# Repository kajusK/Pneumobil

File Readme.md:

Pneumobil control and telemetry system
======================================

This repository contains source code and board design for control system
of pneumobil racing car Falcon from Brno University of Technology.

Parts
-----
 * HMI - Human Machine Interface - LCD touch screen and telemetry board

 * ECU - Engine Control Unit - Control system of pneumatic propulsion system

 * SDU - Speed Display Unit

 * PSU - Power Supply Unit

 * Radio2usb - Telemetry receiving system

Description
-----------
Placement in the car

Python telemetry program

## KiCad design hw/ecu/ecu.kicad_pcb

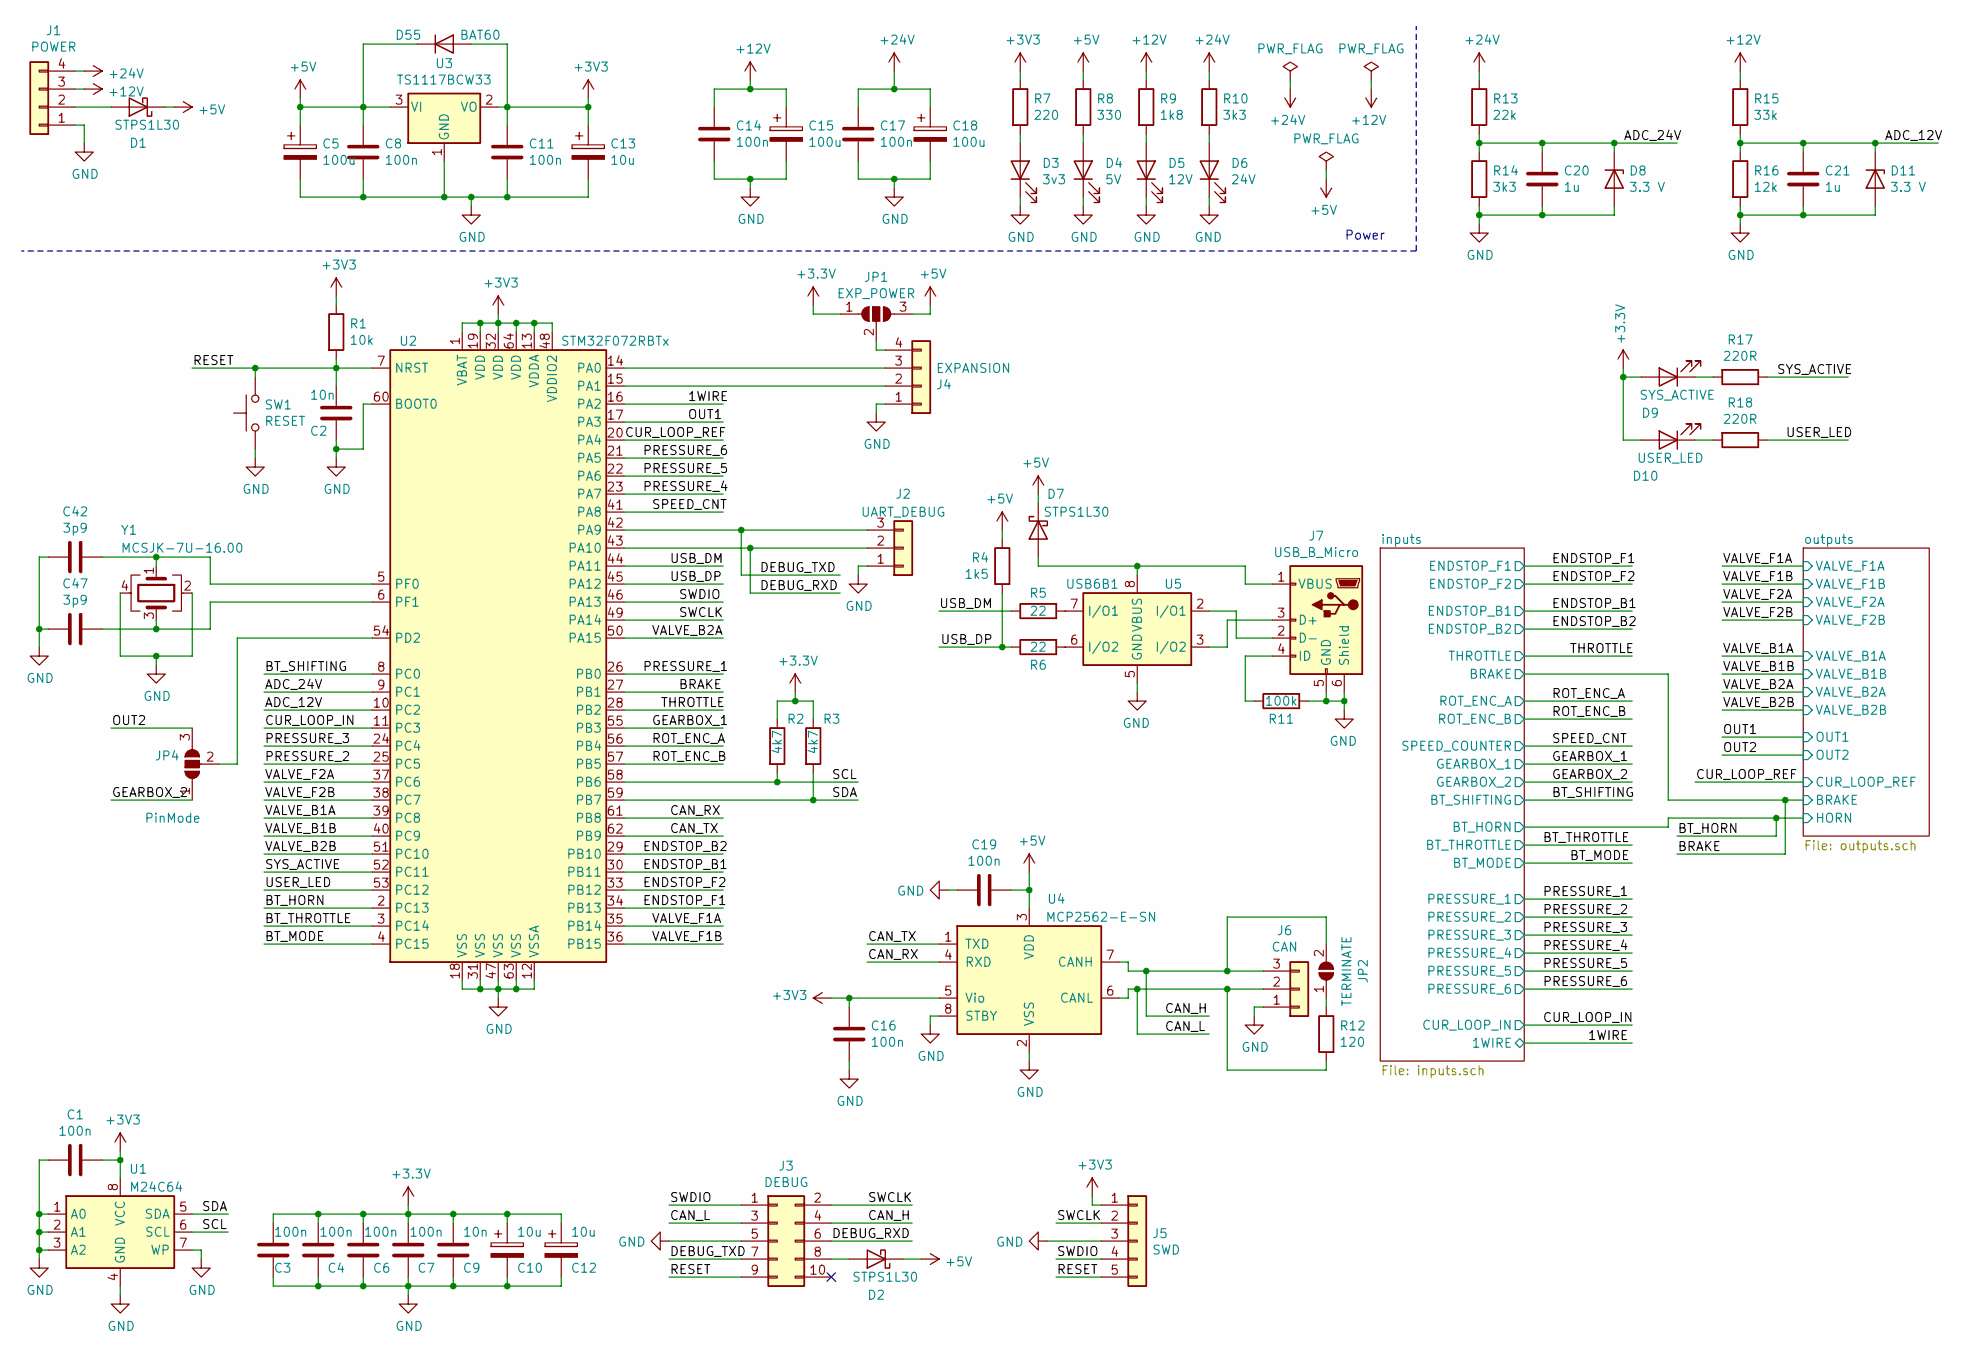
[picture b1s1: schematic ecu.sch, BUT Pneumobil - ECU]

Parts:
C1, C3, C4, C6, C7, C8, C11, C14, C16, C17, C19: 100n; C_0805_2012Metric
C2, C9: 10n; C_0805_2012Metric
C5, C15, C18: 100u; CP_Elec_6.3x7.7
C10, C12, C13: 10u; C_0805_2012Metric
C20, C21: 1u; C_0805_2012Metric
C42, C47: 3p9; C_0805_2012Metric
D1, D2, D7: STPS1L30; D_SMB
D3: 3v3; LED_1206_3216Metric
D4: 5V; LED_1206_3216Metric
D5: 12V; LED_1206_3216Metric
D6: 24V; LED_1206_3216Metric
D8, D11: 3.3 V; D_SOD-523
D9: SYS_ACTIVE; LED_1206_3216Metric
D10: USER_LED; LED_1206_3216Metric
D55: BAT60; D_SOD-323
J1: POWER; PhoenixContact_MCV_1,5_4-G-3.5_1x04_P3.50mm_Vertical
J2: UART_DEBUG; PinHeader_1x03_P2.54mm_Vertical
J3: DEBUG; IDC-Header_2x05_P2.54mm_Vertical
J4: EXPANSION; Molex_KK-254_AE-6410-04A_1x04_P2.54mm_Vertical
J5: SWD; PinHeader_1x05_P2.54mm_Vertical
J6: CAN; Molex_Nano-Fit_105309-xx03_1x03_P2.50mm_Vertical
J7: USB_B_Micro; USB_Micro-B_Molex-105133-0001
JP1: EXP_POWER; SolderJumper-3_P1.3mm_Open_Pad1.0x1.5mm_NumberLabels
JP2: TERMINATE; SolderJumper-2_P1.3mm_Open_Pad1.0x1.5mm
JP4: PinMode; SolderJumper-3_P1.3mm_Open_Pad1.0x1.5mm
R1: 10k; R_0805_2012Metric
R2, R3: 4k7; R_0805_2012Metric
R4: 1k5; R_0805_2012Metric
R5, R6: 22; R_0805_2012Metric
R7: 220; R_0805_2012Metric
R8: 330; R_0805_2012Metric
R9: 1k8; R_0805_2012Metric
R10, R14: 3k3; R_0805_2012Metric
R11: 100k; R_0805_2012Metric
R12: 120; R_0805_2012Metric
R13: 22k; R_0805_2012Metric
R15: 33k; R_0805_2012Metric
R16: 12k; R_0805_2012Metric
R17, R18: 220R; R_0805_2012Metric
SW1: RESET; SW_SPST_PTS645
U1: M24C64; SOIC-8_3.9x4.9mm_P1.27mm
U2: STM32F072RBTx; LQFP-64_10x10mm_P0.5mm
U3: TS1117BCW33; SOT-223-3_TabPin2
U4: MCP2562-E-SN; SOIC-8_3.9x4.9mm_P1.27mm
U5: USB6B1; SOIC-8_3.9x4.9mm_P1.27mm
Y1: MCSJK-7U-16.00; Crystal_SMD_3225-4Pin_3.2x2.5mm

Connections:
+5V: C5.1, C8.1, C19.1, D1.1 (K), D2.1 (K), D7.1 (K), D55.1 (K), JP1.3 (B), R4.1, R8.1, U3.3 (VI), U4.3 (VDD)
+12V: C14.1, C15.1, J1.3, R9.1, R15.1; also elsewhere on the board
+24V: C17.1, C18.1, J1.4, R10.1, R13.1; also elsewhere on the board
/1WIRE: U2.16 (PA2); also elsewhere on the board
/ADC_12V: C21.1, D11.1 (K), R15.2, R16.1, U2.10 (PC2)
/ADC_24V: C20.1, D8.1 (K), R13.2, R14.1, U2.9 (PC1)
/BRAKE: U2.27 (PB1); also elsewhere on the board
/BT_HORN: U2.2 (PC13); also elsewhere on the board
/BT_MODE: U2.4 (PC15); also elsewhere on the board
/BT_SHIFTING: U2.8 (PC0); also elsewhere on the board
/BT_THROTTLE: U2.3 (PC14); also elsewhere on the board
/CAN_H: J3.4, J6.3, JP2.2 (B), U4.7 (CANH)
/CAN_L: J3.3, J6.2, R12.2, U4.6 (CANL)
/CAN_RX: U2.61 (PB8), U4.4 (RXD)
/CAN_TX: U2.62 (PB9), U4.1 (TXD)
/CUR_LOOP_IN: U2.11 (PC3); also elsewhere on the board
/CUR_LOOP_REF: U2.20 (PA4); also elsewhere on the board
/DEBUG_RXD: J2.2, J3.6, U2.43 (PA10)
/DEBUG_TXD: J2.3, J3.7, U2.42 (PA9)
/ENDSTOP_B1: U2.30 (PB11); also elsewhere on the board
/ENDSTOP_B2: U2.29 (PB10); also elsewhere on the board
/ENDSTOP_F1: U2.34 (PB13); also elsewhere on the board
/ENDSTOP_F2: U2.33 (PB12); also elsewhere on the board
/GEARBOX_1: U2.55 (PB3); also elsewhere on the board
/GEARBOX_2: JP4.1 (A); also elsewhere on the board
/OUT1: U2.17 (PA3); also elsewhere on the board
/OUT2: JP4.3 (B); also elsewhere on the board
/PRESSURE_1: U2.26 (PB0); also elsewhere on the board
/PRESSURE_2: U2.25 (PC5); also elsewhere on the board
/PRESSURE_3: U2.24 (PC4); also elsewhere on the board
/PRESSURE_4: U2.23 (PA7); also elsewhere on the board
/PRESSURE_5: U2.22 (PA6); also elsewhere on the board
/PRESSURE_6: U2.21 (PA5); also elsewhere on the board
/RESET: C2.1, J3.9, J5.5, R1.2, SW1.2, U2.7 (NRST)
/ROT_ENC_A: U2.56 (PB4); also elsewhere on the board
/ROT_ENC_B: U2.57 (PB5); also elsewhere on the board
/SCL: R2.2, U1.6 (SCL), U2.58 (PB6)
/SDA: R3.2, U1.5 (SDA), U2.59 (PB7)
/SPEED_CNT: U2.41 (PA8); also elsewhere on the board
/SWCLK: J3.2, J5.2, U2.49 (PA14)
/SWDIO: J3.1, J5.4, U2.46 (PA13)
/SYS_ACTIVE: R17.1, U2.52 (PC11)
/THROTTLE: U2.28 (PB2); also elsewhere on the board
/USB_DM: R5.1, U2.44 (PA11)
/USB_DP: R4.2, R6.1, U2.45 (PA12)
/USER_LED: R18.1, U2.53 (PC12)
/VALVE_B1A: U2.39 (PC8); also elsewhere on the board
/VALVE_B1B: U2.40 (PC9); also elsewhere on the board
/VALVE_B2A: U2.50 (PA15); also elsewhere on the board
/VALVE_B2B: U2.51 (PC10); also elsewhere on the board
/VALVE_F1A: U2.35 (PB14); also elsewhere on the board
/VALVE_F1B: U2.36 (PB15); also elsewhere on the board
/VALVE_F2A: U2.37 (PC6); also elsewhere on the board
/VALVE_F2B: U2.38 (PC7); also elsewhere on the board
GND: C1.2, C2.2, C3.2, C4.2, C5.2, C6.2, C7.2, C8.2, C9.2, C10.2, C11.2, C12.2, C13.2, C14.2, C15.2, C16.2, C17.2, C18.2, C19.2, C20.2, C21.2, C42.2, C47.2, D3.1 (K), D4.1 (K), D5.1 (K), D6.1 (K), D8.2 (A), D11.2 (A), J1.1, J2.1, J3.5, J4.1, J5.3, J6.1, J7.5 (GND), J7.6 (Shield), R11.2, R14.2, R16.2, SW1.1, U1.1 (A0), U1.2 (A1), U1.3 (A2), U1.4 (GND), U1.7 (WP), U2.12 (VSSA), U2.18 (VSS), U2.31 (VSS), U2.47 (VSS), U2.60 (BOOT0), U2.63 (VSS), U3.1 (GND), U4.2 (VSS), U4.8 (STBY), U5.4 (GND), U5.5 (GND), Y1.2, Y1.4; also elsewhere on the board
unnamed: C42.1, U2.5 (PF0), Y1.1
unnamed: C47.1, U2.6 (PF1), Y1.3
unnamed: D1.2 (A), J1.2
unnamed: D2.2 (A), J3.8
unnamed: D3.2 (A), R7.2
unnamed: D4.2 (A), R8.2
unnamed: D5.2 (A), R9.2
unnamed: D6.2 (A), R10.2
unnamed: D7.2 (A), J7.1 (VBUS), U5.1 (VBUS), U5.8 (VBUS)
unnamed: D9.1 (K), R17.2
unnamed: D10.1 (K), R18.2
unnamed: J4.2, U2.15 (PA1)
unnamed: J4.3, U2.14 (PA0)
unnamed: J4.4, JP1.2 (C)
unnamed: J7.2 (D-), U5.2 (I/O1)
unnamed: J7.3 (D+), U5.3 (I/O2)
unnamed: J7.4 (ID), R11.1
unnamed: JP2.1 (A), R12.1
unnamed: JP4.2 (C), U2.54 (PD2)
unnamed: R5.2, U5.7 (I/O1)
unnamed: R6.2, U5.6 (I/O2)

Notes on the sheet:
Power

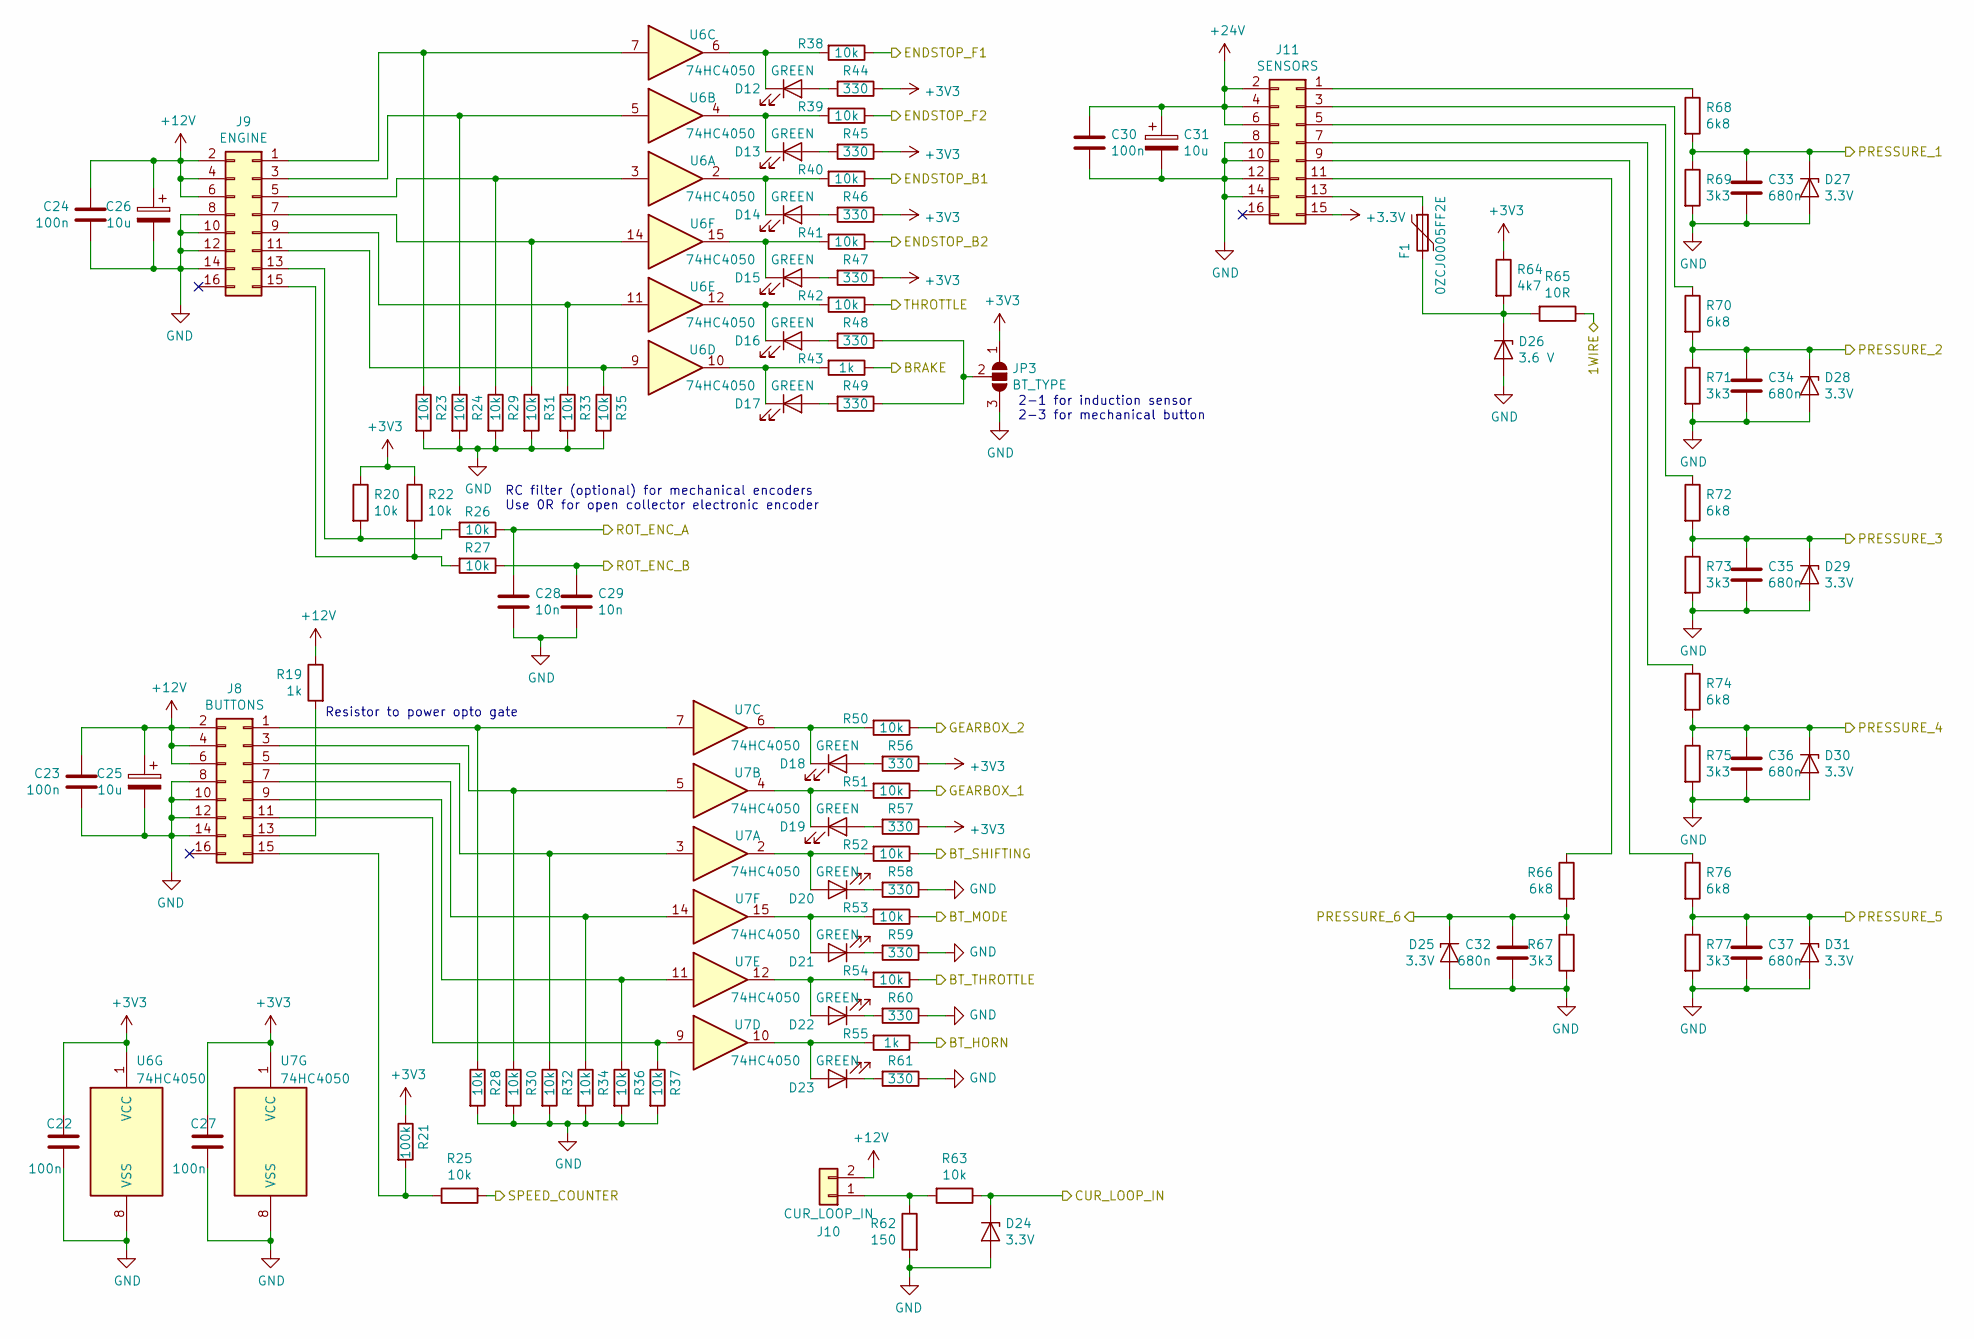
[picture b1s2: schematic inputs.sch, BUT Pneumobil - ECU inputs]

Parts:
C22, C23, C24, C27, C30: 100n; C_0805_2012Metric
C25, C26, C31: 10u; C_0805_2012Metric
C28, C29: 10n; C_0805_2012Metric
C32, C33, C34, C35, C36, C37: 680n; C_0805_2012Metric
D12, D13, D14, D15, D16, D17, D18, D19, D20, D21, D22, D23: GREEN; LED_1206_3216Metric
D24, D25, D27, D28, D29, D30, D31: 3.3V; D_SOD-523
D26: 3.6 V; D_MELF
F1: 0ZCJ0005FF2E; Fuse_1206_3216Metric
J8: BUTTONS; IDC-Header_2x08_P2.54mm_Vertical_Lock
J9: ENGINE; IDC-Header_2x08_P2.54mm_Vertical_Lock
J10: CUR_LOOP_IN; PhoenixContact_MCV_1,5_2-G-3.5_1x02_P3.50mm_Vertical
J11: SENSORS; IDC-Header_2x08_P2.54mm_Vertical_Lock
JP3: BT_TYPE; SolderJumper-3_P1.3mm_Open_Pad1.0x1.5mm
R19, R43, R55: 1k; R_0805_2012Metric
R20, R22, R23, R24, R25, R26, R27, R28, R29, R30, R31, R32, R33, R34, R35, R36, R37, R38, R39, R40, R41, R42, R50, R51, R52, R53, R54, R63: 10k; R_0805_2012Metric
R21: 100k; R_0805_2012Metric
R44, R45, R46, R47, R48, R49, R56, R57, R58, R59, R60, R61: 330; R_0805_2012Metric
R62: 150; R_0805_2012Metric
R64: 4k7; R_0805_2012Metric
R65: 10R; R_0805_2012Metric
R66, R68, R70, R72, R74, R76: 6k8; R_0805_2012Metric
R67, R69, R71, R73, R75, R77: 3k3; R_0805_2012Metric
U6, U7: 74HC4050; SOIC-16_3.9x9.9mm_P1.27mm

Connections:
+12V: C23.1, C24.1, C25.1, C26.1, J8.2, J8.4, J8.6, J9.2, J9.4, J9.6, J10.2, R19.1; also elsewhere on the board
+24V: C30.1, C31.1, J11.2, J11.4, J11.6; also elsewhere on the board
/1WIRE: R65.1; also elsewhere on the board
/BRAKE: R43.1; also elsewhere on the board
/BT_HORN: R55.1; also elsewhere on the board
/BT_MODE: R53.1; also elsewhere on the board
/BT_SHIFTING: R52.1; also elsewhere on the board
/BT_THROTTLE: R54.1; also elsewhere on the board
/CUR_LOOP_IN: D24.1 (K), R63.1; also elsewhere on the board
/ENDSTOP_B1: R40.1; also elsewhere on the board
/ENDSTOP_B2: R41.1; also elsewhere on the board
/ENDSTOP_F1: R38.1; also elsewhere on the board
/ENDSTOP_F2: R39.1; also elsewhere on the board
/GEARBOX_1: R51.1; also elsewhere on the board
/GEARBOX_2: R50.1; also elsewhere on the board
/PRESSURE_1: C33.1, D27.1 (K), R68.2, R69.1; also elsewhere on the board
/PRESSURE_2: C34.1, D28.1 (K), R70.2, R71.1; also elsewhere on the board
/PRESSURE_3: C35.1, D29.1 (K), R72.2, R73.1; also elsewhere on the board
/PRESSURE_4: C36.1, D30.1 (K), R74.2, R75.1; also elsewhere on the board
/PRESSURE_5: C37.1, D31.1 (K), R76.2, R77.1; also elsewhere on the board
/PRESSURE_6: C32.1, D25.1 (K), R66.2, R67.1; also elsewhere on the board
/ROT_ENC_A: C28.1, R26.1; also elsewhere on the board
/ROT_ENC_B: C29.1, R27.1; also elsewhere on the board
/SPEED_CNT: R25.2; also elsewhere on the board
/THROTTLE: R42.1; also elsewhere on the board
GND: C22.2, C23.2, C24.2, C25.2, C26.2, C27.2, C28.2, C29.2, C30.2, C31.2, C32.2, C33.2, C34.2, C35.2, C36.2, C37.2, D24.2 (A), D25.2 (A), D26.2 (A), D27.2 (A), D28.2 (A), D29.2 (A), D30.2 (A), D31.2 (A), J8.8, J8.10, J8.12, J8.14, J9.8, J9.10, J9.12, J9.14, J11.8, J11.10, J11.12, J11.14, JP3.3 (B), R23.2, R24.2, R28.2, R29.2, R30.2, R31.2, R32.2, R33.2, R34.2, R35.2, R36.2, R37.2, R58.1, R59.1, R60.1, R61.1, R62.2, R67.2, R69.2, R71.2, R73.2, R75.2, R77.2, U6.8 (VSS), U7.8 (VSS); also elsewhere on the board
unnamed: D12.1 (K), R38.2, U6.6
unnamed: D12.2 (A), R44.2
unnamed: D13.1 (K), R39.2, U6.4
unnamed: D13.2 (A), R45.2
unnamed: D14.1 (K), R40.2, U6.2
unnamed: D14.2 (A), R46.2
unnamed: D15.1 (K), R41.2, U6.15
unnamed: D15.2 (A), R47.2
unnamed: D16.1 (K), R42.2, U6.12
unnamed: D16.2 (A), R48.2
unnamed: D17.1 (K), R43.2, U6.10
unnamed: D17.2 (A), R49.2
unnamed: D18.1 (K), R50.2, U7.6
unnamed: D18.2 (A), R56.2
unnamed: D19.1 (K), R51.2, U7.4
unnamed: D19.2 (A), R57.2
unnamed: D20.1 (K), R58.2
unnamed: D20.2 (A), R52.2, U7.2
unnamed: D21.1 (K), R59.2
unnamed: D21.2 (A), R53.2, U7.15
unnamed: D22.1 (K), R60.2
unnamed: D22.2 (A), R54.2, U7.12
unnamed: D23.1 (K), R61.2
unnamed: D23.2 (A), R55.2, U7.10
unnamed: D26.1 (K), F1.2, R64.2, R65.2
unnamed: F1.1, J11.13
unnamed: J8.1, R28.1, U7.7
unnamed: J8.3, R30.1, U7.5
unnamed: J8.5, R32.1, U7.3
unnamed: J8.7, R34.1, U7.14
unnamed: J8.9, R36.1, U7.11
unnamed: J8.11, R37.1, U7.9
unnamed: J8.13, R19.2
unnamed: J8.15, R21.2, R25.1
unnamed: J9.1, R23.1, U6.7
unnamed: J9.3, R24.1, U6.5
unnamed: J9.5, R29.1, U6.3
unnamed: J9.7, R31.1, U6.14
unnamed: J9.9, R33.1, U6.11
unnamed: J9.11, R35.1, U6.9
unnamed: J9.13, R20.2, R26.2
unnamed: J9.15, R22.2, R27.2
unnamed: J10.1, R62.1, R63.2
unnamed: J11.1, R68.1
unnamed: J11.3, R70.1
unnamed: J11.5, R72.1
unnamed: J11.7, R74.1
unnamed: J11.9, R76.1
unnamed: J11.11, R66.1
unnamed: JP3.2 (C), R48.1, R49.1

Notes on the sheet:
Resistor to power opto gate
RC filter (optional) for mechanical encoders Use 0R for open collector electronic encoder
2-1 for induction sensor 2-3 for mechanical button

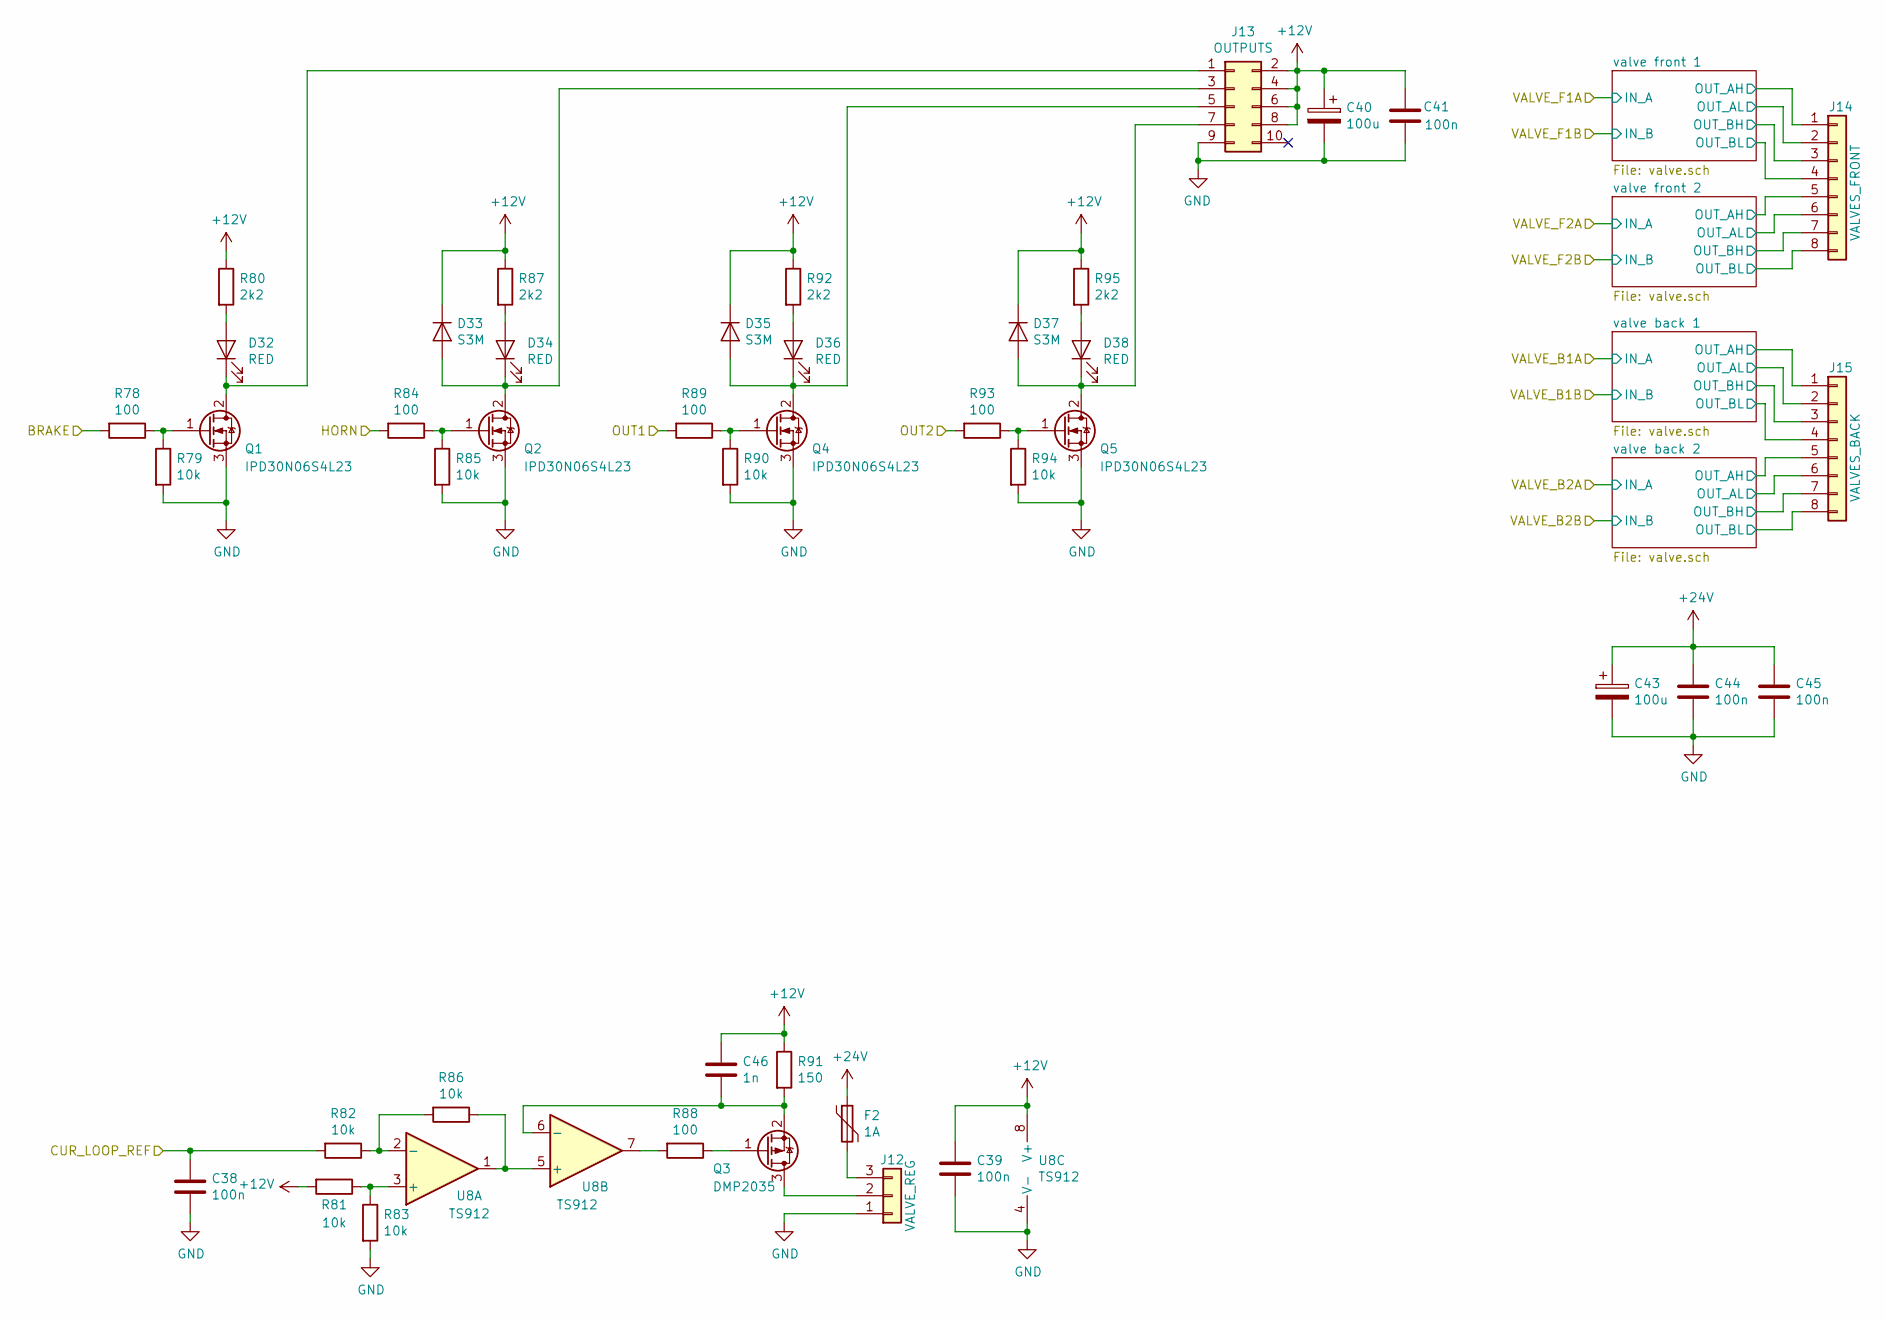
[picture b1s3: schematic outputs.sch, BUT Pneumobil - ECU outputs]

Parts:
C38, C39, C41, C44, C45: 100n; C_0805_2012Metric
C40, C43: 100u; CP_Elec_6.3x7.7
C46: 1n; C_0805_2012Metric
D32, D34, D36, D38: RED; LED_1206_3216Metric
D33, D35, D37: S3M; D_SMB
F2: 1A; Fuse_1206_3216Metric
J12: VALVE_REG; PhoenixContact_MCV_1,5_3-G-3.5_1x03_P3.50mm_Vertical
J13: OUTPUTS; IDC-Header_2x05_P2.54mm_Vertical_Lock
J14: VALVES_FRONT; PhoenixContact_MCV_1,5_8-G-3.5_1x08_P3.50mm_Vertical
J15: VALVES_BACK; PhoenixContact_MCV_1,5_8-G-3.5_1x08_P3.50mm_Vertical
Q1, Q2, Q4, Q5: IPD30N06S4L23; TO-252-2
Q3: DMP2035; SOT-23
R78, R84, R88, R89, R93: 100; R_0805_2012Metric
R79, R81, R82, R83, R85, R86, R90, R94: 10k; R_0805_2012Metric
R80, R87, R92, R95: 2k2; R_0805_2012Metric
R91: 150; R_0805_2012Metric
U8: TS912; SOIC-8_3.9x4.9mm_P1.27mm

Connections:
+12V: C39.1, C40.1, C41.1, C46.1, D33.1 (K), D35.1 (K), D37.1 (K), J13.2, J13.4, J13.6, J13.8, R80.1, R81.2, R87.1, R91.1, R92.1, R95.1, U8.8 (V+); also elsewhere on the board
+24V: C43.1, C44.1, C45.1, F2.1, J14.1, J14.3, J14.5, J14.7, J15.1, J15.3, J15.5, J15.7; also elsewhere on the board
/BRAKE: R78.2; also elsewhere on the board
/BT_HORN: R84.2; also elsewhere on the board
/CUR_LOOP_REF: C38.1, R82.2; also elsewhere on the board
/OUT1: R89.2; also elsewhere on the board
/OUT2: R93.2; also elsewhere on the board
/outputs/valve back 1/OUT_AL: J15.2; also elsewhere on the board
/outputs/valve back 1/OUT_BL: J15.4; also elsewhere on the board
/outputs/valve back 2/OUT_AL: J15.6; also elsewhere on the board
/outputs/valve back 2/OUT_BL: J15.8; also elsewhere on the board
/outputs/valve front 1/OUT_AL: J14.2; also elsewhere on the board
/outputs/valve front 1/OUT_BL: J14.4; also elsewhere on the board
/outputs/valve front 2/OUT_AL: J14.6; also elsewhere on the board
/outputs/valve front 2/OUT_BL: J14.8; also elsewhere on the board
GND: C38.2, C39.2, C40.2, C41.2, C43.2, C44.2, C45.2, J12.1, J13.9, Q1.3 (S), Q2.3 (S), Q4.3 (S), Q5.3 (S), R79.2, R83.2, R85.2, R90.2, R94.2, U8.4 (V-); also elsewhere on the board
unnamed: C46.2, Q3.2 (S), R91.2, U8.6 (-)
unnamed: D32.1 (K), J13.1, Q1.2 (D)
unnamed: D32.2 (A), R80.2
unnamed: D33.2 (A), D34.1 (K), J13.3, Q2.2 (D)
unnamed: D34.2 (A), R87.2
unnamed: D35.2 (A), D36.1 (K), J13.5, Q4.2 (D)
unnamed: D36.2 (A), R92.2
unnamed: D37.2 (A), D38.1 (K), J13.7, Q5.2 (D)
unnamed: D38.2 (A), R95.2
unnamed: F2.2, J12.3
unnamed: J12.2, Q3.3 (D)
unnamed: Q1.1 (G), R78.1, R79.1
unnamed: Q2.1 (G), R84.1, R85.1
unnamed: Q3.1 (G), R88.1
unnamed: Q4.1 (G), R89.1, R90.1
unnamed: Q5.1 (G), R93.1, R94.1
unnamed: R81.1, R83.1, U8.3 (+)
unnamed: R82.1, R86.2, U8.2 (-)
unnamed: R86.1, U8.1, U8.5 (+)
unnamed: R88.2, U8.7

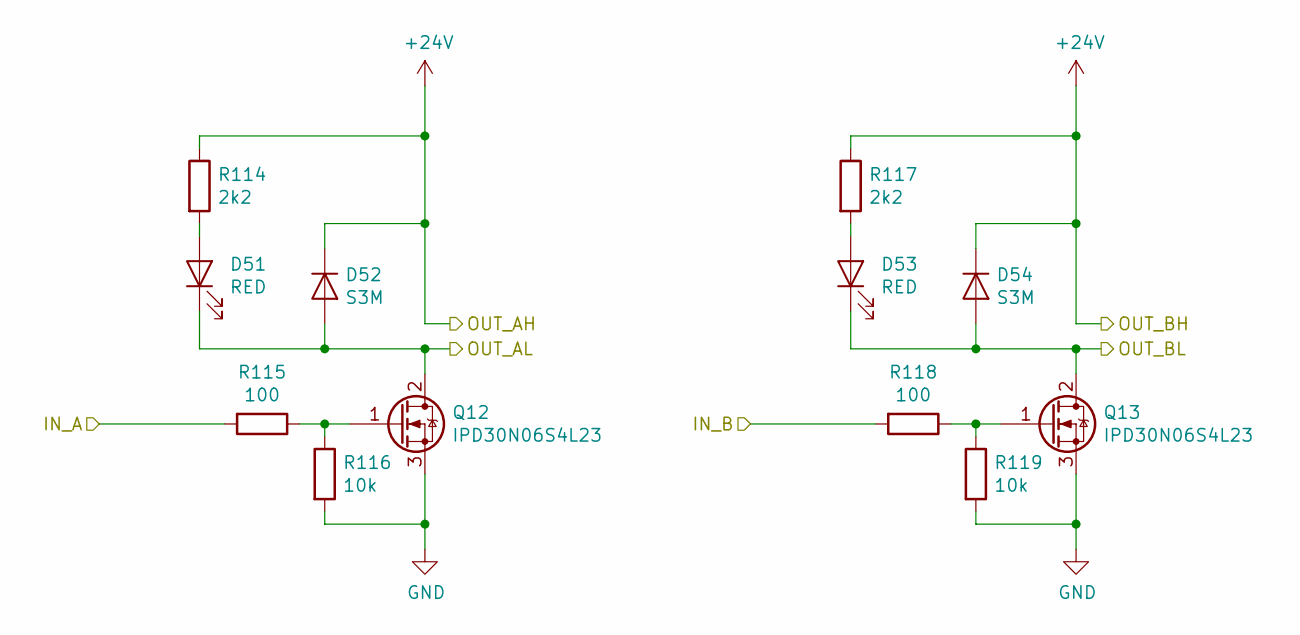
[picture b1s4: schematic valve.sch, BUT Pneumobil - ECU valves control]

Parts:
D39, D41: RED; LED_1206_3216Metric
D40, D42: S3M; D_SMB
Q6, Q7: IPD30N06S4L23; TO-252-2
R96, R99: 2k2; R_0805_2012Metric
R97, R100: 100; R_0805_2012Metric
R98, R101: 10k; R_0805_2012Metric

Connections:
+24V: D40.1 (K), D42.1 (K), R96.1, R99.1; also elsewhere on the board
/VALVE_F1A: R97.2; also elsewhere on the board
/VALVE_F1B: R100.2; also elsewhere on the board
/outputs/valve front 1/OUT_AL: D39.1 (K), D40.2 (A), Q6.2 (D); also elsewhere on the board
/outputs/valve front 1/OUT_BL: D41.1 (K), D42.2 (A), Q7.2 (D); also elsewhere on the board
GND: Q6.3 (S), Q7.3 (S), R98.2, R101.2; also elsewhere on the board
unnamed: D39.2 (A), R96.2
unnamed: D41.2 (A), R99.2
unnamed: Q6.1 (G), R97.1, R98.1
unnamed: Q7.1 (G), R100.1, R101.1

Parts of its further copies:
D43, D45, D47, D49, D51, D53: RED; LED_1206_3216Metric
D44, D46, D48, D50, D52, D54: S3M; D_SMB
Q8, Q9, Q10, Q11, Q12, Q13: IPD30N06S4L23; TO-252-2
R102, R105, R108, R111, R114, R117: 2k2; R_0805_2012Metric
R103, R106, R109, R112, R115, R118: 100; R_0805_2012Metric
R104, R107, R110, R113, R116, R119: 10k; R_0805_2012Metric

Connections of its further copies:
+24V: D44.1 (K), D46.1 (K), D48.1 (K), D50.1 (K), D52.1 (K), D54.1 (K), R102.1, R105.1, R108.1, R111.1, R114.1, R117.1; also elsewhere on the board
/VALVE_B1A: R109.2; also elsewhere on the board
/VALVE_B1B: R112.2; also elsewhere on the board
/VALVE_B2A: R115.2; also elsewhere on the board
/VALVE_B2B: R118.2; also elsewhere on the board
/VALVE_F2A: R103.2; also elsewhere on the board
/VALVE_F2B: R106.2; also elsewhere on the board
/outputs/valve back 1/OUT_AL: D47.1 (K), D48.2 (A), Q10.2 (D); also elsewhere on the board
/outputs/valve back 1/OUT_BL: D49.1 (K), D50.2 (A), Q11.2 (D); also elsewhere on the board
/outputs/valve back 2/OUT_AL: D51.1 (K), D52.2 (A), Q12.2 (D); also elsewhere on the board
/outputs/valve back 2/OUT_BL: D53.1 (K), D54.2 (A), Q13.2 (D); also elsewhere on the board
/outputs/valve front 2/OUT_AL: D43.1 (K), D44.2 (A), Q8.2 (D); also elsewhere on the board
/outputs/valve front 2/OUT_BL: D45.1 (K), D46.2 (A), Q9.2 (D); also elsewhere on the board
GND: Q8.3 (S), Q9.3 (S), Q10.3 (S), Q11.3 (S), Q12.3 (S), Q13.3 (S), R104.2, R107.2, R110.2, R113.2, R116.2, R119.2; also elsewhere on the board
unnamed: D43.2 (A), R102.2
unnamed: D45.2 (A), R105.2
unnamed: D47.2 (A), R108.2
unnamed: D49.2 (A), R111.2
unnamed: D51.2 (A), R114.2
unnamed: D53.2 (A), R117.2
unnamed: Q8.1 (G), R103.1, R104.1
unnamed: Q9.1 (G), R106.1, R107.1
unnamed: Q10.1 (G), R109.1, R110.1
unnamed: Q11.1 (G), R112.1, R113.1
unnamed: Q12.1 (G), R115.1, R116.1
unnamed: Q13.1 (G), R118.1, R119.1

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
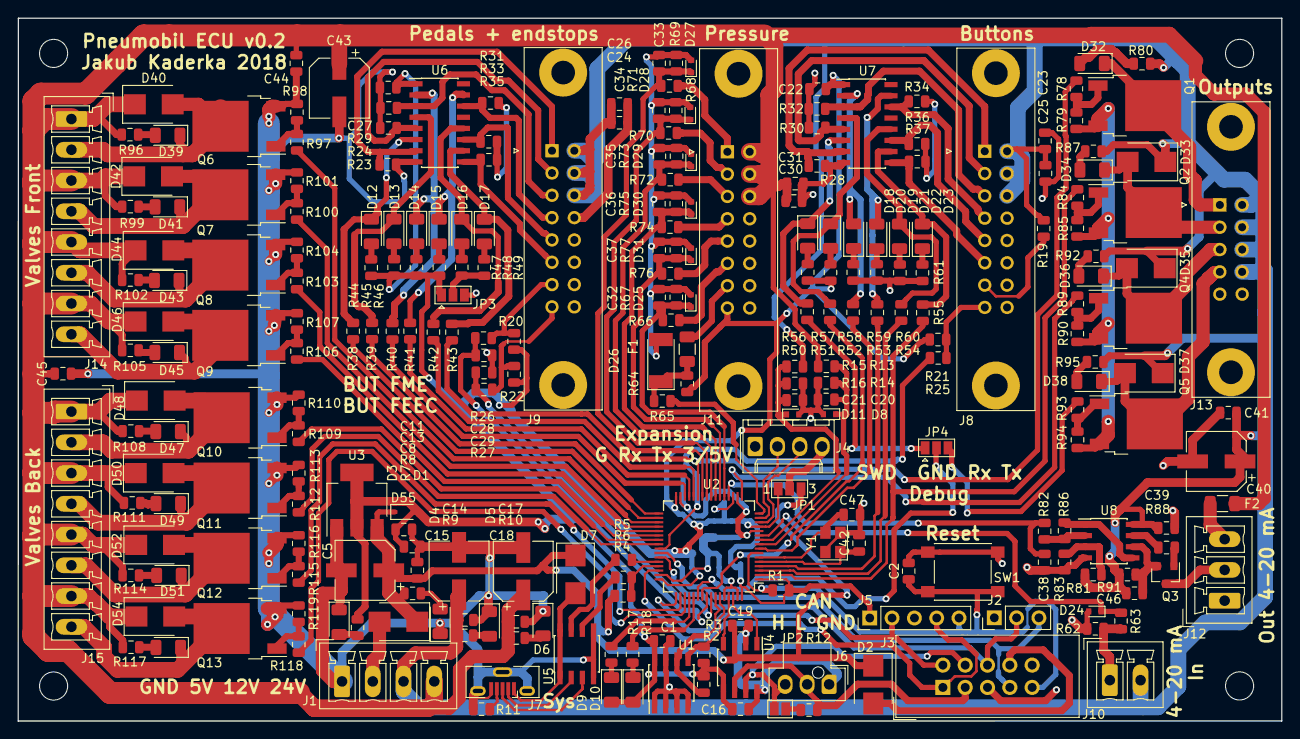
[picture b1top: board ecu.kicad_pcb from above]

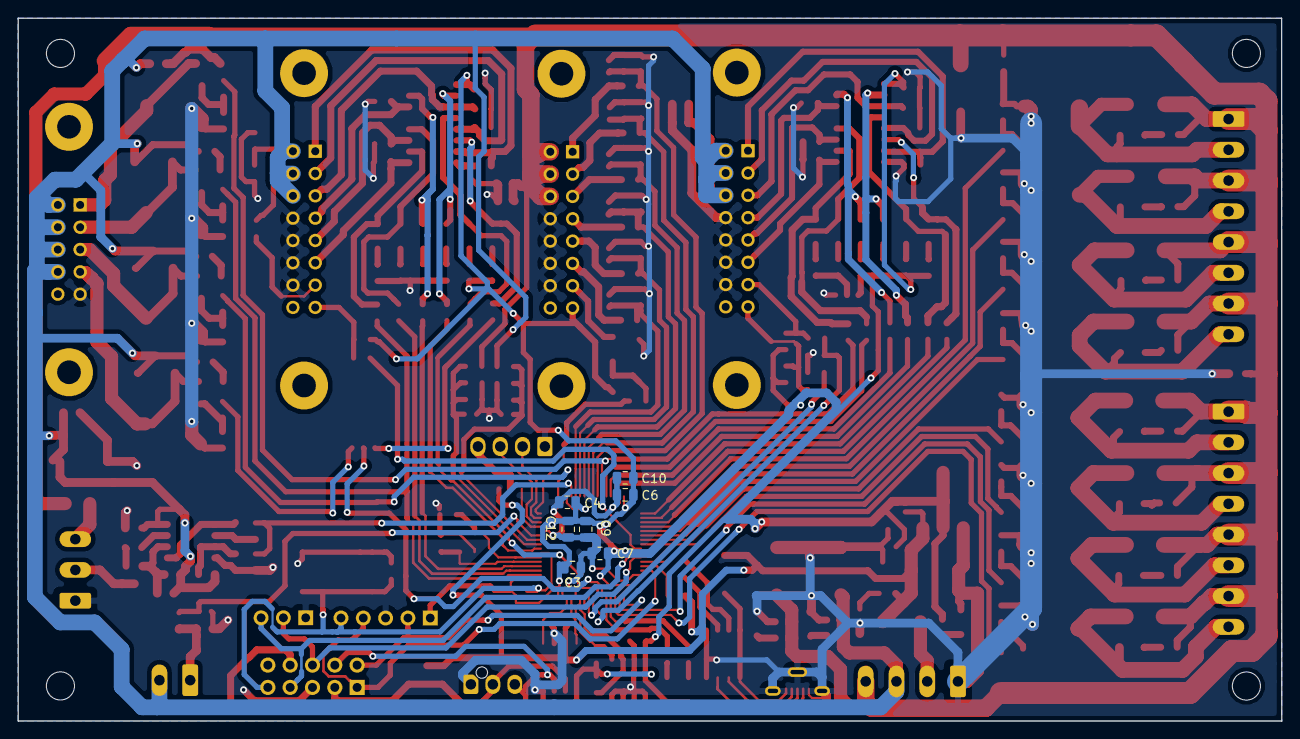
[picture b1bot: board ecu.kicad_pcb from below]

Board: 2 copper layers, 143.8 x 80.0 mm, 265 parts (7 on the bottom side), 171 nets.
